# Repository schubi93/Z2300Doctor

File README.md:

## Saving my Logitech Z-2300 stereo

> Because the climate and the biosphere don’t care about our politics and our empty words for a single second. They only care about what we actually do.
> 
> -- <cite>Greta Thunberg, 2020</cite>

I bought a stereo, specifically the [Logitech Z2300](https://productz.com/de/logitech-z-2300/p/nxxLn) a few years ago and loved it.
Unfortunately, the volume knob is making use of an analog potentiometer.
And as you may have guessed - it failed!

But I don't want to scrap it, as I affirm the [Right to Repair](https://repair.eu/) and want to save some money as well as ressources.
Hence, this project was born...

## Situation

The stereo consists of ~~three~~ four main components:
1. 2 speaker to sit on the desk
2. a subwoofer
3. a control satellite to sit on your desk
4. the power amplifier inside the subwoofer

As part of this project, I need a new control satellite.
As the current tendency is to clean up your desk, I don't want any additional hardware sitting on my desk.
Hence, controlling the volume is done from my pc, resulting in a less complex PCB and also overcoming conflicts with the original design.

In further designs, I may include a MCU for additional functions, such as Bluetooth or ADC for light control of e.g. LED strips, dependent on the volume.
If you feel like going forward to it, feel free to fork!

## Overview

* [control_pcb](control_pcb/): Contains the [KiCad](https://www.kicad.org/) project as well as Gerber Data and the BOM
* [power_amplifier](power_amplifier/Readme.md): Write-Up of reworking the amplifier - stay tuned for updates!
* [misc](misc/Readme.md): Logo, unrelated stuff...

## License

This project is licensed under the `MIT` License.
`CERN OHL` was also thought of, but I'm not aware of every detail of the license.
I'll try to comply to the [reuse](https://reuse.software/) strategy in later stages of the project.

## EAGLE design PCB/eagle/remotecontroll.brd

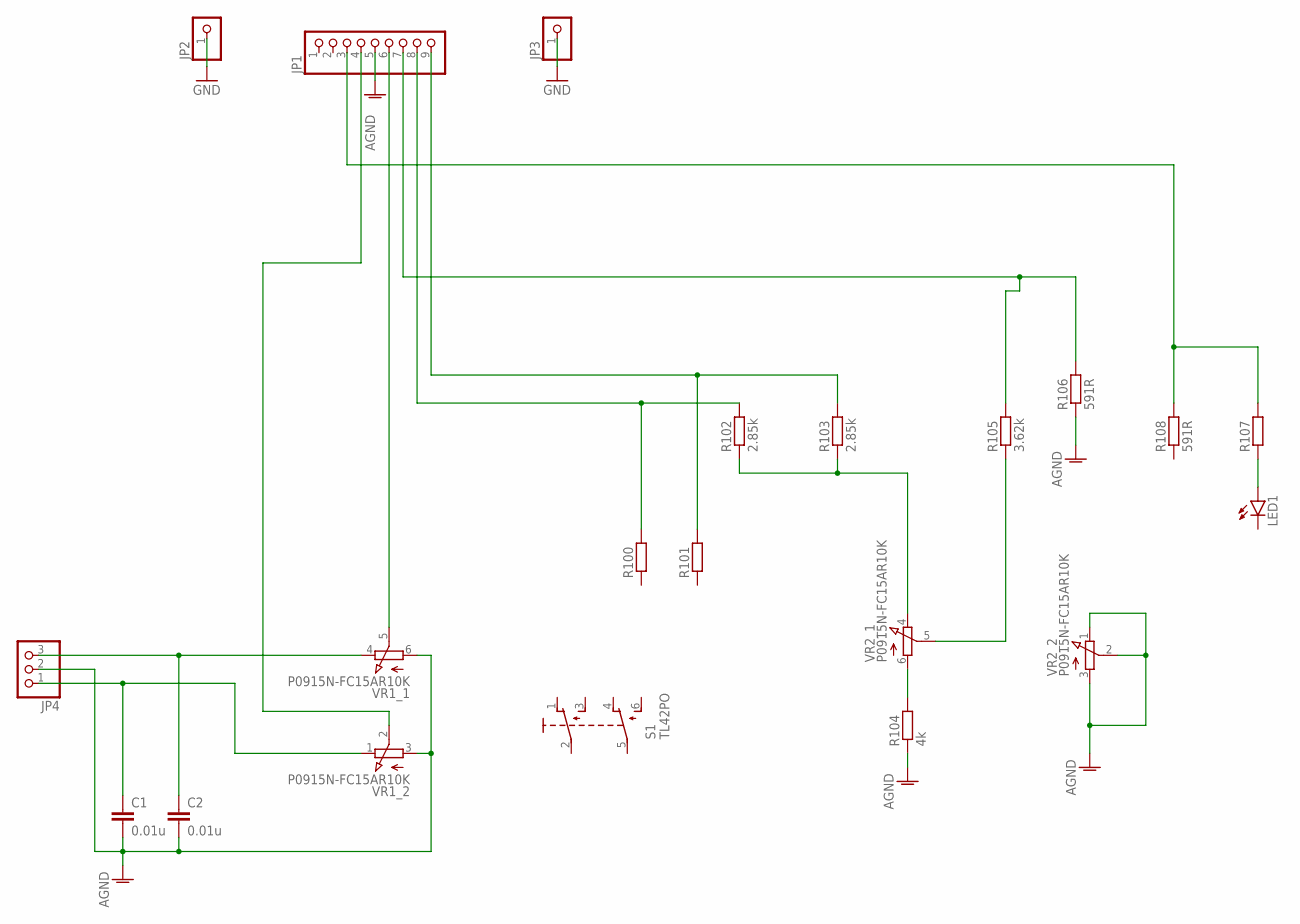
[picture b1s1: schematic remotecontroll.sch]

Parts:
C1, C2: 0.01u; C0603
JP1: PINHD-1X9; 1X09
JP2, JP3: PINHD-1X1; 1X01
JP4: PINHD-1X3; 1X03
LED1: LED3MM
R100, R101, R107: R-EU_0207/10; 0207/10
R102, R103: 2.85k; 0204/7
R104: 4k; 0204/7
R105: 3.62k; 0204/7
R106, R108: 591R; 0204/7
S1: TL42PO; TL4XPO
VR1, VR2: P0915N-FC15AR10K; P0915NFC15AR10K

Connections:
AGND: C1.2, C2.2, JP1.5, JP4.2, R104.1, R106.1, VR1.3 (A), VR1.6 (A), VR2.1 (E), VR2.2 (S), VR2.3 (A)
GND: JP2.1, JP3.1
unnamed: JP1.6, VR1.5 (S)
unnamed: C2.1, JP4.3, VR1.4 (E)
unnamed: C1.1, JP4.1, VR1.1 (E)
unnamed: JP1.4, VR1.2 (S)
unnamed: JP1.7, R105.2, R106.2
unnamed: JP1.8, R100.2, R102.2
unnamed: JP1.9, R101.2, R103.2
unnamed: LED1.A, R107.1
unnamed: JP1.3, R107.2, R108.2
unnamed: R104.2, VR2.6 (A)
unnamed: R105.1, VR2.5 (S)
unnamed: R102.1, R103.1, VR2.4 (E)

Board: 2 copper layers, 19 parts (0 on the bottom side), 14 nets, no tracks yet.

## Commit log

2019-06-26 initial commit; created README.md
2019-06-26 added .gitignore for eagle
2019-06-26 added previously developed eagle schematic and board
2019-06-26 added parts.txt for partnumbers
2019-06-26 reformated parts file
2019-06-29 added KiCad project
2021-12-18 :seedling: starting the project again
2021-12-18 removed Eagle project
2021-12-18 renamed folders to small letters
2021-12-18 typo correction
2021-12-18 added BOM
2021-12-18 added overview section
2021-12-18 adding some infos
2021-12-18 added misc folder
2021-12-18 gitignore cleanup from Eagle
2021-12-18 updated logo path
2021-12-18 :seedling: License
2021-12-18 added readme about power amplifier and renamed dirs
